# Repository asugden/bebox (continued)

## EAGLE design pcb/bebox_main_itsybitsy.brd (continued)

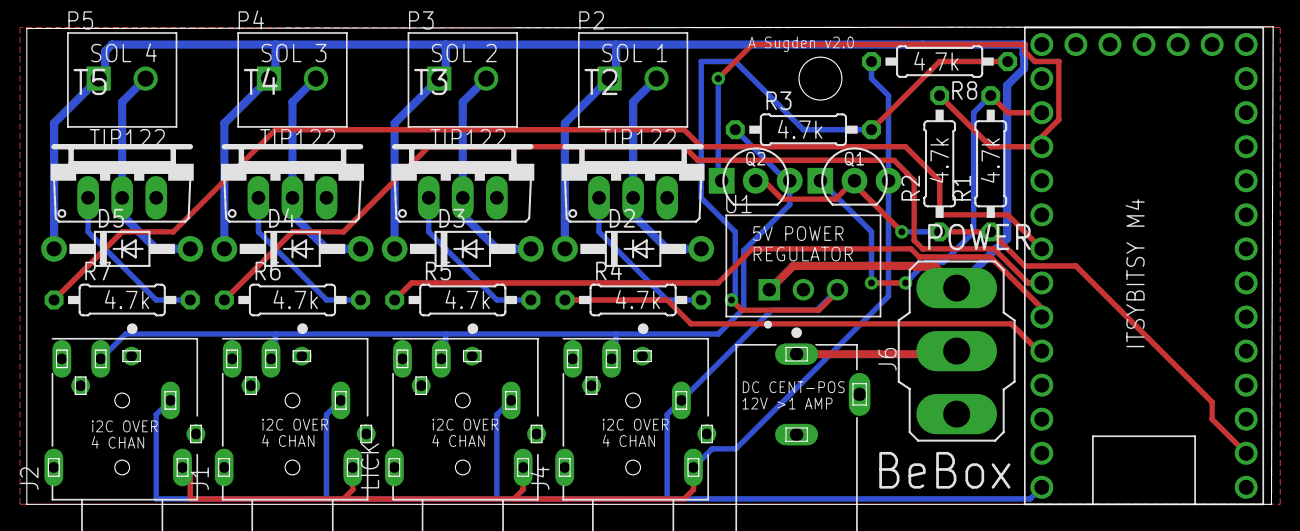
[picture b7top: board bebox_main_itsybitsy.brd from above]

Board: 2 copper layers, 92.9 x 35.6 mm, 30 parts (0 on the bottom side), 21 nets.

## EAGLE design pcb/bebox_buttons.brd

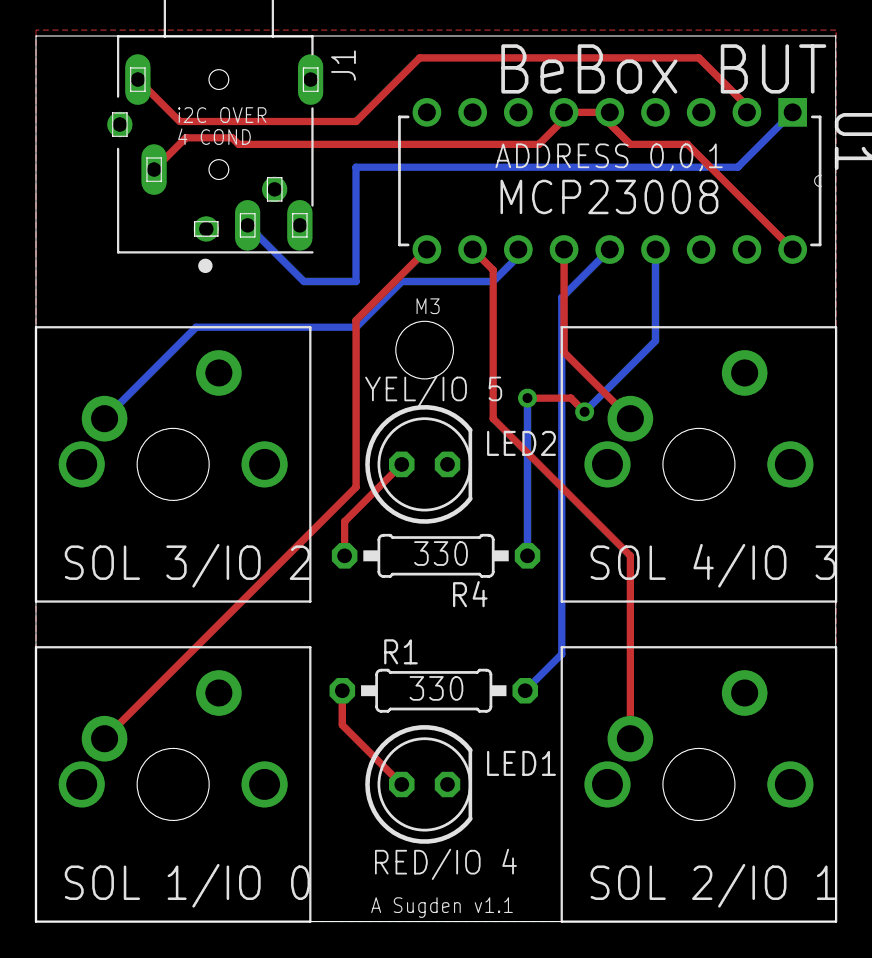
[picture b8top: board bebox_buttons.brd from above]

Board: 2 copper layers, 44.4 x 49.2 mm, 10 parts (0 on the bottom side), 12 nets.

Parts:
J1: SJ-435107RS; CUI_SJ-435107RS
LED1, LED2: LED5MM
R1, R4: 330; 0207/10
U1: MCP23008-E/P; DIP254P762X533-18
U$2, U$3, U$4, U$5: CHERRY-MX

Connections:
5V: J1.2, U1.5, U1.6, U1.18
GND: J1.1, LED1.K, LED2.K, U1.3, U1.4, U1.9, U$2.SW2, U$3.SW2, U$4.SW2, U$5.SW2
unnamed: U1.10, U$5.SW1
unnamed: U1.11, U$4.SW1
unnamed: U1.12, U$3.SW1
unnamed: U1.13, U$2.SW1
unnamed: LED1.A, R1.1
unnamed: R1.2, U1.14
unnamed: LED2.A, R4.2
unnamed: J1.4, U1.2
unnamed: R4.1, U1.15
SCL: J1.3, U1.1

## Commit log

2019-01-22 Completed but untested boards. Note that there is an extra solenoid position.
2019-01-22 Updated to version 1.1 a BNC board that connects to the main board via i2c. It is untested but complete.
2019-01-22 Updated Readme to introduce Bebox.
2019-01-22 Version 1.1 of a completed but untested daughterboard that registers licks and controls solenoids.
2019-01-22 Ignore temporary files.
2019-01-22 Files necessary for the wheel and associated components.
2019-01-22 Necessary files for controlling the arduino in the boards.
2019-01-22 Updated to describe all files.
2019-01-22 Testing markdown.
2019-01-22 Updating markdown.
2019-01-22 Moved PCB files to their own location.
2019-01-28 Added encoder codes.
2019-01-28 Updated the README to include the encoder.
2019-01-28 Added lickspout files and definitions.
2019-03-15 Updated the boards.
2019-03-15 Updated the arduino code to correctly reflect dumberbox.
2019-03-15 Moved arduino files into their own directories.
2019-03-15 Updated formatting.
2019-03-15 Updated to include encoder board.
2019-03-15 Added subdirectory readme.
2019-03-15 Added some parts numbers.
2019-03-15 Updated to include all components necessary for the current boards.
2019-03-15 Minor updates.
2019-03-15 Added info about the syringe pump.
2019-03-15 Updated to include syringe pump hardware.
2019-04-10 Working BeBox code.
2019-04-11 Renamed original bebox main and udpated the footprint of the switch.
2019-04-11 Added new bebox main that works with 3.3V Adafruit Itsy Bitsy, which is the replacement for the now depracated Pro Trinket.
2019-04-11 Updated screenprints.
2019-04-11 Completed syringe pump board and schematic.
2019-04-11 Completed spritzer board and schematic.
2019-04-11 Completed and tested versions of each of the three BeBox containers.
2019-04-12 Updated readmes.
2019-04-12 Added cable information
2019-04-12 Added lickspout borad color matching.
2019-04-14 Have updated the Arduino code and it is confirmed to work.
2019-04-14 Now have created boards that should directly connect to cables connected to the national instruments PCIe boards, rather than passing through the BNC box.
2019-04-15 Previously did not have sufficient analog inputs for two photometry inputs and one digital input. Now have 4 BNC inputs.
2019-04-17 Fixed minor bug.
2019-04-17 Fixed overlap of wires to Solenoid 1 and Solenoid 2
2019-04-17 Reorderd pins so that they would be more general across users.
2019-05-01 Added testing code.
2019-05-01 Added Spritz. Requires its own Encoder library because the current version does not work with a SAMD51, i.e. ItsyBitsy M4.
2019-05-10 Updated readme.
2019-05-10 Updated spacing of syringe pump and added copy of encoder library due to version issues.
